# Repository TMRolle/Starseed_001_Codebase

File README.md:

# Starseed_001_Codebase
Codebase for the Starseed 001 facility.

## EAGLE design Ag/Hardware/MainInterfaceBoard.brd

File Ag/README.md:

Agricultural Automation codebase for Starseed 001

The current agricultural computation and control setup consists of a number of devices.
Central to the setup is a Raspberry Pi running the latest version of Raspbian. This runs an MQTT broker and coordinates all the peripheral devices over a network.
One or more NodeMCU modules are used to interface with all the sensors and actuators. Shift register modules are used to expand the available number of devices.
An arduino nano is used as an interface for the AC dimmer switch(es), as an inexpensive way to offload the task of z-crossing from the NodeMCU modules.

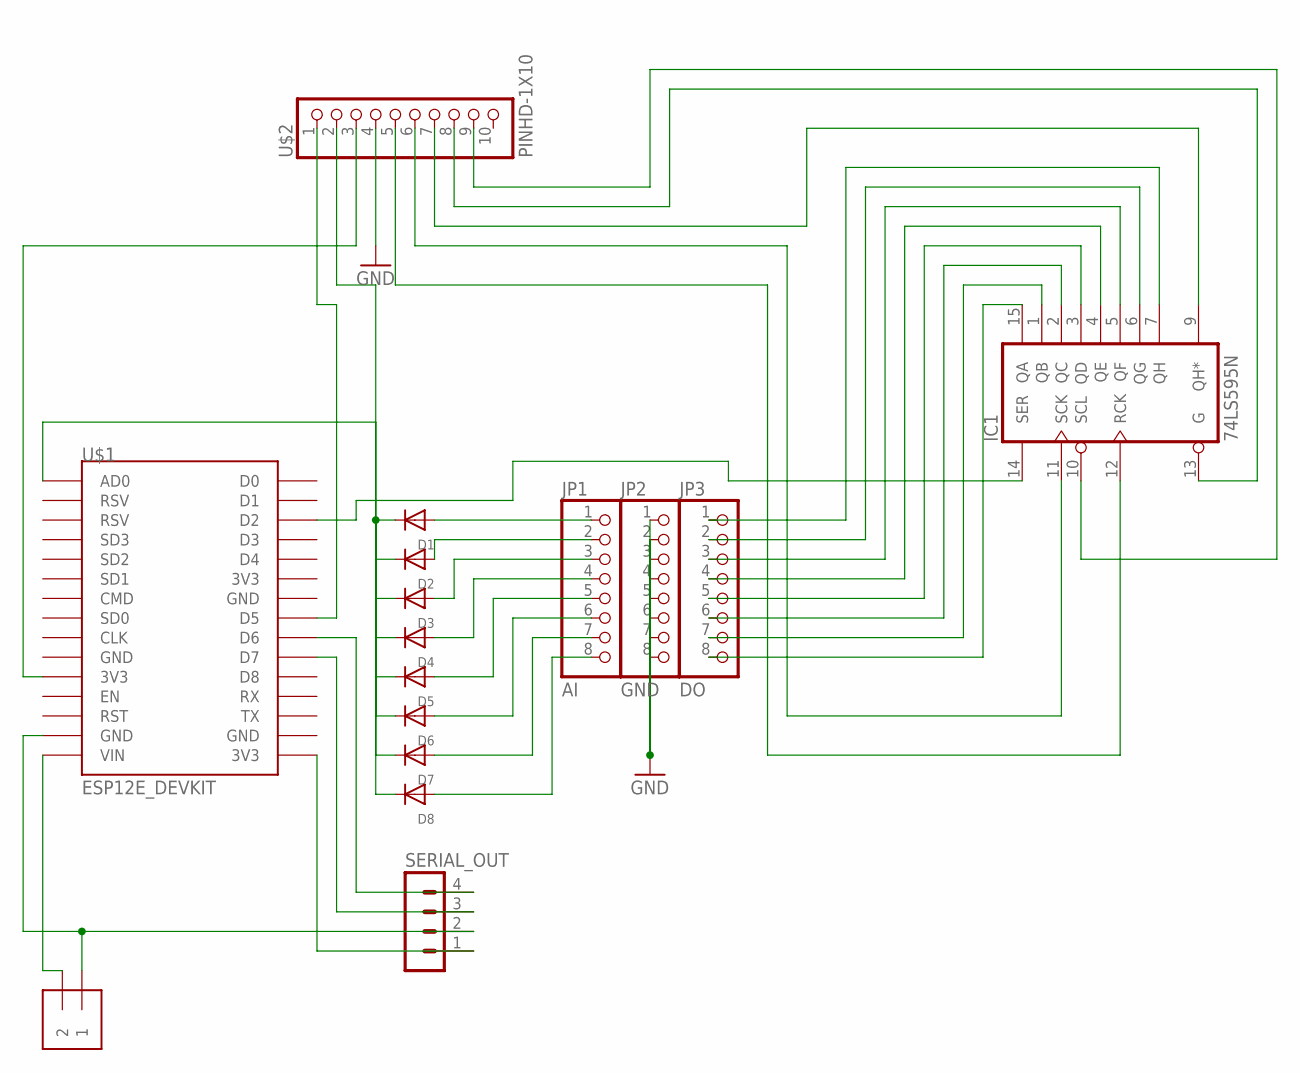
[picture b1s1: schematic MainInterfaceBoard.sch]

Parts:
D1, D2, D3, D4, D5, D6, D7, D8: DIODEDO-1N4148; DO-1N4148
IC1: 74LS595N; DIL16
J2: 1X2-3.5MM
JP1: AI; 1X08-CLEANBIG
JP2: GND; 1X08-CLEANBIG
JP3: DO; 1X08-CLEANBIG
SERIAL_OUT: MA04-1
U$1: ESP12E_DEVKIT
U$2: PINHD-1X10; 1X10-BIG

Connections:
GND: IC1.8 (GND), JP2.1, JP2.2, JP2.3, JP2.4, JP2.5, JP2.6, JP2.7, JP2.8, U$2.4
unnamed: IC1.15 (QA), JP3.8
unnamed: IC1.1 (QB), JP3.7
unnamed: IC1.2 (QC), JP3.6
unnamed: IC1.3 (QD), JP3.5
unnamed: IC1.4 (QE), JP3.4
unnamed: IC1.5 (QF), JP3.3
unnamed: IC1.6 (QG), JP3.2
unnamed: D1.C, D2.C, D3.C, D4.C, D5.C, D6.C, D7.C, D8.C, U$1.AD0, U$2.2
unnamed: IC1.7 (QH), JP3.1
unnamed: D7.A, JP1.7
unnamed: D6.A, JP1.6
unnamed: D4.A, JP1.4
unnamed: D5.A, JP1.5
unnamed: D3.A, JP1.3
unnamed: D2.A, JP1.2
unnamed: D8.A, JP1.8
unnamed: D1.A, JP1.1
unnamed: IC1.9 (QH*), U$2.7
unnamed: U$1.D5, U$2.1
unnamed: IC1.12 (RCK), U$2.5
unnamed: U$1.3V3@0 (3V3), U$2.3
unnamed: IC1.10 (SCL), U$2.9
unnamed: IC1.11 (SCK), U$2.6
unnamed: IC1.14 (SER), U$1.D2
unnamed: IC1.13 (G), U$2.8
unnamed: SERIAL_OUT.4, U$1.D6
unnamed: SERIAL_OUT.3, U$1.D7
unnamed: SERIAL_OUT.1, U$1.3V3@2 (3V3)
unnamed: J2.1, SERIAL_OUT.2, U$1.GND@1 (GND)
unnamed: J2.2, U$1.VIN
VCC: IC1.16 (VCC)

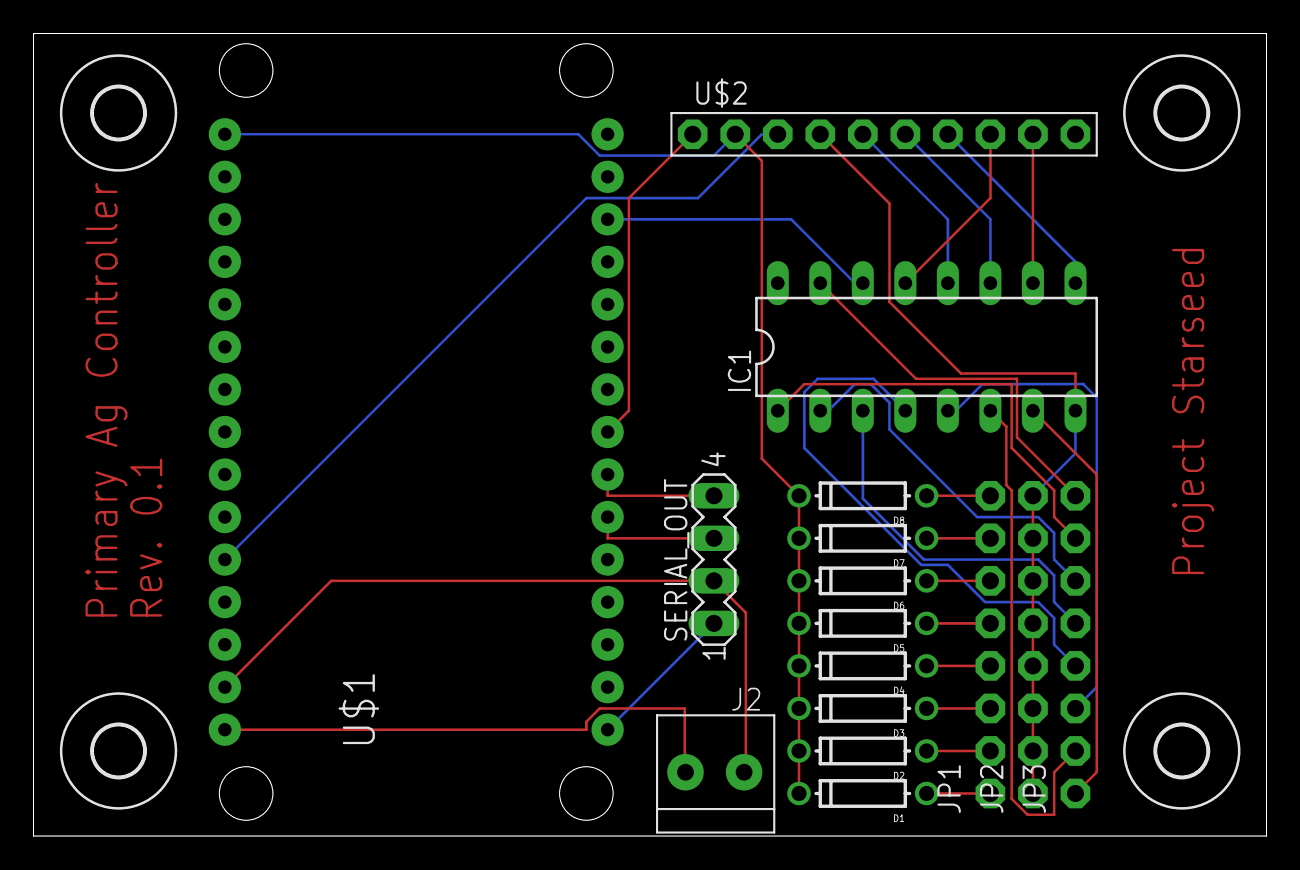
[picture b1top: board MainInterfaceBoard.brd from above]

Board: 2 copper layers, 73.6 x 47.9 mm, 20 parts (0 on the bottom side), 31 nets.

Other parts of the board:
U$3, U$4, U$5, U$6: 3,0

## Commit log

2018-01-13 Ag folder
2018-01-13 ag readme
2018-01-13 Uploading all the existing code
2018-01-13 docs
2018-01-13 Prettying up code
2018-01-14 Adding DHT and Software Serial funcionality (untested)
2018-01-18 Adding Eagle PCB schematic and board design for main board
